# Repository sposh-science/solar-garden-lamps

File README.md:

# solar-lanterns
Design files for automatic solar garden lanterns used at Science Hack Day, Belgaum 2016

Top Side Screenshot |  Bottom Side Screenshot
 --------------------------- | ---------------------------------
    |  

This board was designed by [CSpark Research](https://github.com/csparkresearch) for Science Hack Day, Belgaum , 2016.

It consists of the following elementary components
+ Barrel Jack for plugging in the solar panel
+ 6V/1W solar panel
+ Custom mounting holes for rechargeable 4V/400mAh lead acid battery
+ 2N7000 MOSFET to turn on the LEDs only if the battery is not being charged (no sunlight present)
+ 2x current limiting resistors
+ 4x LEDs (5mm white)
+ 1x RGB LED/any other alternate light source
+ 1x Slider switch to select between the 4x LEDs or the alternate LED light

It is intended as a tool to enhance soldering skills, as well to create a usable garden lamp that charges by day, and lights up by night

Happy Hacking! :)

## Dependencies
+ [KiCad EDA](http://kicad.org/)

Rendered Gerber files are present in the `Gerber` directory

[License](./LICENSE.txt): GPLv3

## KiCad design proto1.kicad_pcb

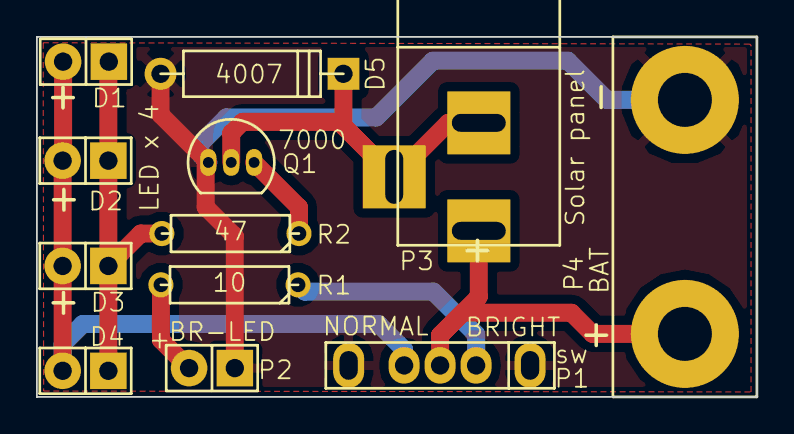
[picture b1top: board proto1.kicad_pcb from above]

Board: 2 copper layers, 40.0 x 20.0 mm, 12 parts (0 on the bottom side), 8 nets.

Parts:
D1, D2, D3, D4: LED; Pin_Header_Straight_1x02
D5: 4007; D4
P1: sw; switch-2way
P2: BR-LED; Pin_Header_Straight_1x02
P3: Solar panel; BARREL_JACK
P4: BAT; bat-LA
Q1: 7000; TO-92_Inline_Narrow_Oval
R1: 10; R3
R2: 47; R3

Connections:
/+BAT: P1.3, P3.1, P4.2
GND: D5.2, P1.1, P1.5, P2.1, P4.1, Q1.1
unnamed: D1.1, D2.1, D3.1, D4.1, R2.2
unnamed: D1.2, D2.2, D3.2, D4.2, P1.4
unnamed: D5.1, P3.2, P3.3, Q1.2
unnamed: P1.2, R1.1
unnamed: P2.2, R1.2
unnamed: Q1.3, R2.1

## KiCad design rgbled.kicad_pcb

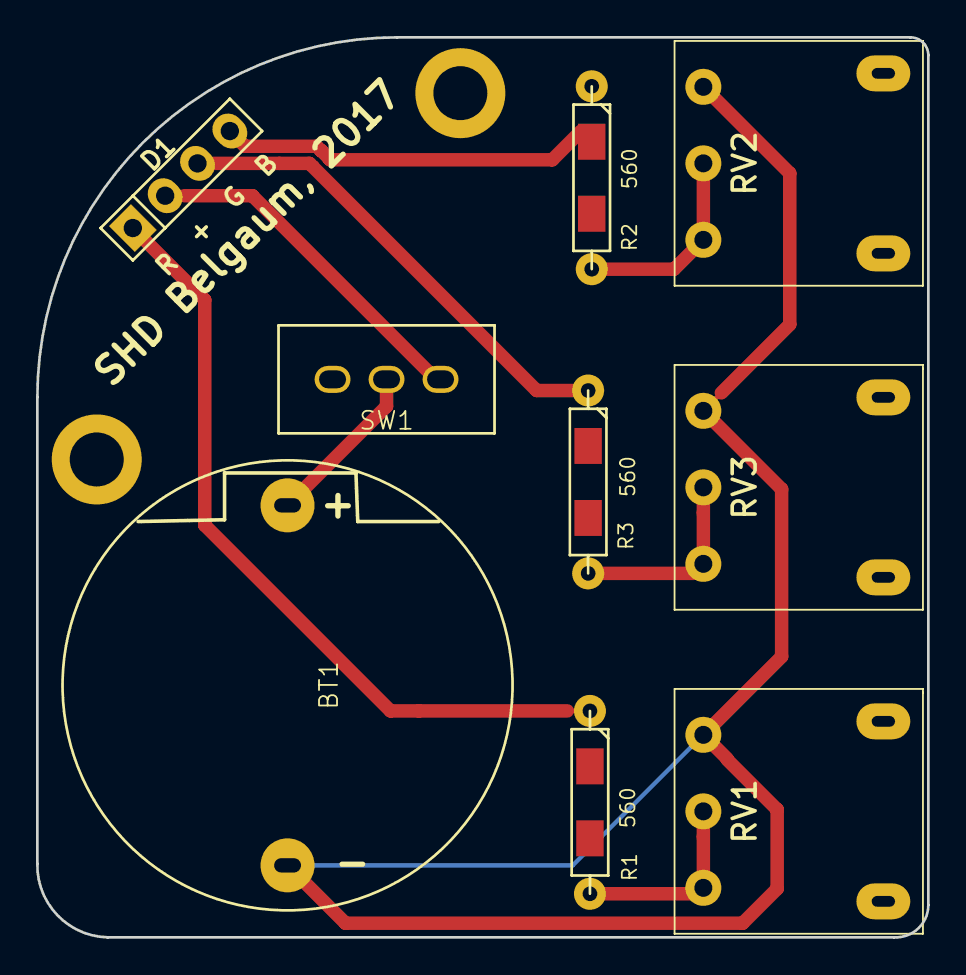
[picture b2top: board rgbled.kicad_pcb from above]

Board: 2 copper layers, 49.5 x 50.0 mm, 11 parts (0 on the bottom side), 9 nets.

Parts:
BT1: Battery; bat-holder
D1: LED_RABG; Pin_Header_Straight_1x04
R1, R2, R3: 560; R4-TH-SMD
RV1, RV2, RV3: 10K; my-slider-pot
SW1: Switch_SPDT_x2; mySwitch-3way
mh1, mh2: MH; MountingHole-3mm

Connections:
GND: BT1.2, RV1.1, RV2.1, RV3.1, mh1.1, mh2.1
unnamed: BT1.1, SW1.2
unnamed: D1.1, R1.1
unnamed: D1.2, SW1.1
unnamed: D1.3, R3.1
unnamed: D1.4, R2.1
unnamed: R1.2, RV1.2, RV1.3
unnamed: R2.2, RV2.2, RV2.3
unnamed: R3.2, RV3.2, RV3.3

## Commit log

2017-10-01 added design files, README, and Gerber
2017-10-01 minor tweak to front side screenshot
2021-11-10 Update README.md
    https://forum.kicad.info/t/warning-avoid-all-links-to-kicad-pcb-org-use-kicad-org/31521
